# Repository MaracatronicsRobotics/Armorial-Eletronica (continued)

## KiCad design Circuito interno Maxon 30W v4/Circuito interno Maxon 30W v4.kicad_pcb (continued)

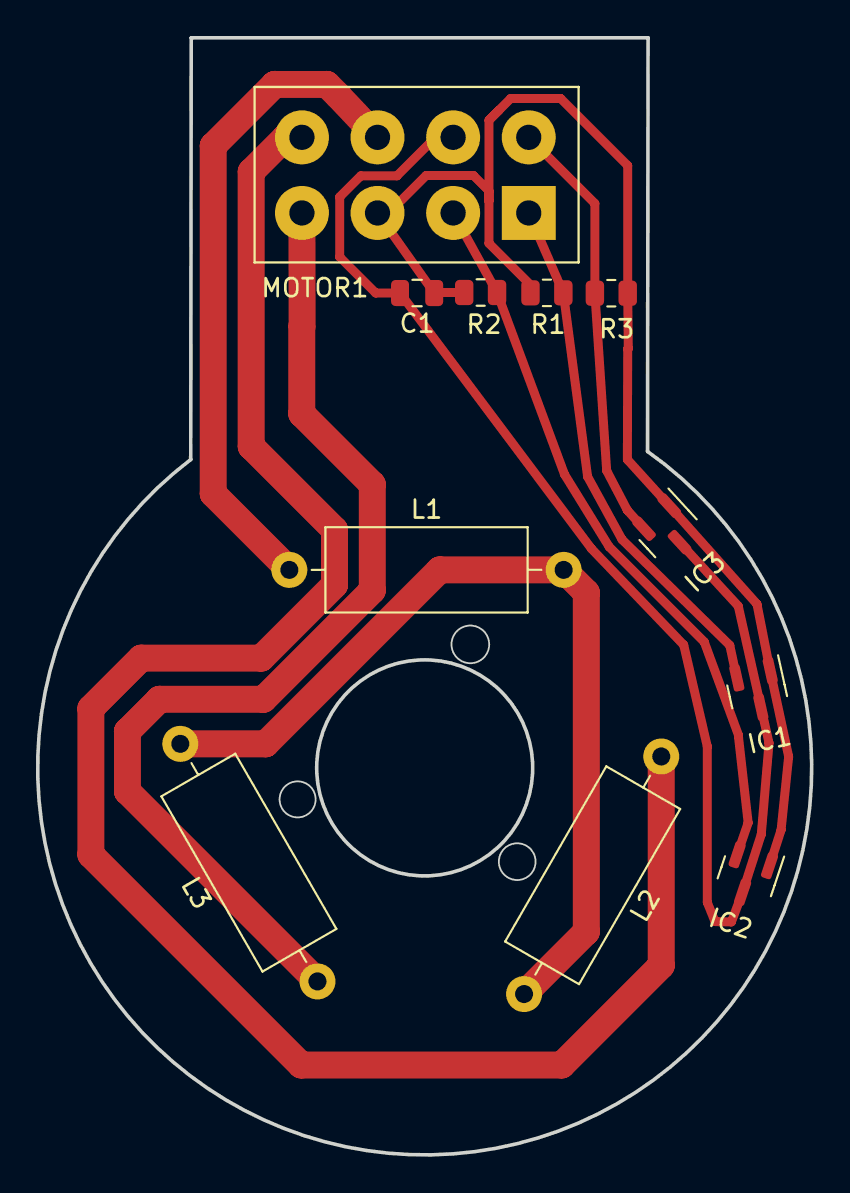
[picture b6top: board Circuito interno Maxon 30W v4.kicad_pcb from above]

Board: 2 copper layers, 43.0 x 62.1 mm, 11 parts (0 on the bottom side), 9 nets.

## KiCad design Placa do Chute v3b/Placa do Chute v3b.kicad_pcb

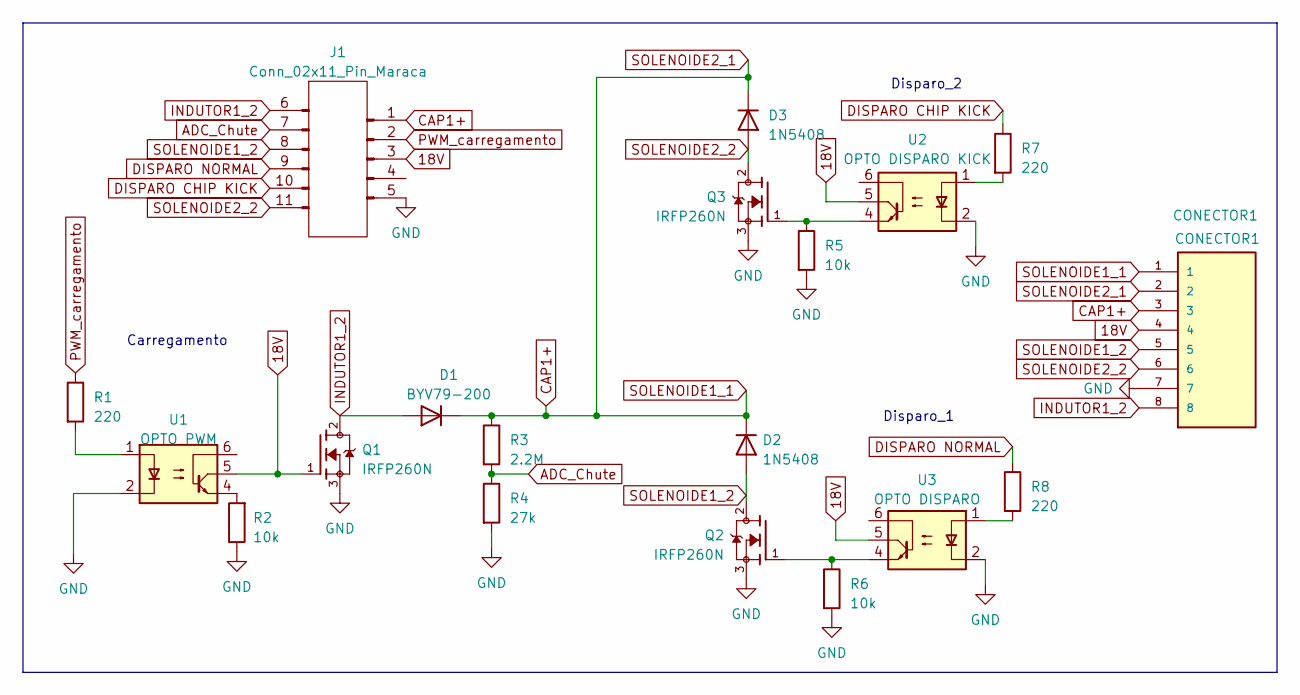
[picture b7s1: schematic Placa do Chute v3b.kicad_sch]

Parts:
CONECTOR1: CONECTOR1; TE_1586037-8b
D1: BYV79-200; TO-220-2_Vertical
D2, D3: 1N5408; D_DO-201AD_P15.24mm_Horizontal
J1: Conn_02x11_Pin_Maraca; Conn_2x11_Maraca_Chute
Q1, Q2, Q3: IRFP260N; TO545P1560X500X2460-3 90d; PARTREV 08/18/10
R1, R7, R8: 220; R_Axial_DIN0207_L6.3mm_D2.5mm_P10.16mm_Horizontal
R2, R5, R6: 10k; R_Axial_DIN0207_L6.3mm_D2.5mm_P10.16mm_Horizontal
R3: 2.2M; R_Axial_DIN0207_L6.3mm_D2.5mm_P10.16mm_Horizontal
R4: 27k; R_Axial_DIN0207_L6.3mm_D2.5mm_P10.16mm_Horizontal
U1: OPTO PWM; DIP-6_W7.62mm
U2: OPTO DISPARO KICK; DIP-6_W7.62mm
U3: OPTO DISPARO; DIP-6_W7.62mm

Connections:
18V: CONECTOR1.4, J1.3, Q1.1, U1.5, U2.5, U3.5
ADC_Chute: J1.7, R3.2, R4.1
CAP1+: CONECTOR1.1, CONECTOR1.2, CONECTOR1.3, D1.1 (K), D2.1 (K), D3.1 (K), J1.1, R3.1
DISPARO CHIP KICK: J1.10, R7.1
DISPARO NORMAL: J1.9, R8.1
GND: CONECTOR1.7, J1.5, Q1.3, Q2.3, Q3.3, R2.1, R4.2, R5.2, R6.2, U1.2, U2.2, U3.2
INDUTOR1_2: CONECTOR1.8, D1.2 (A), J1.6, Q1.2
unnamed: Q2.1, R6.1, U3.4
unnamed: Q3.1, R5.1, U2.4
unnamed: R1.2, U1.1
unnamed: R2.2, U1.4
unnamed: R7.2, U2.1
unnamed: R8.2, U3.1
PWM_carregamento: J1.2, R1.1
SOLENOIDE1_2: CONECTOR1.5, D2.2 (A), J1.8, Q2.2
SOLENOIDE2_2: CONECTOR1.6, D3.2 (A), J1.11, Q3.2

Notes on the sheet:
Disparo_2
Carregamento
Disparo_1

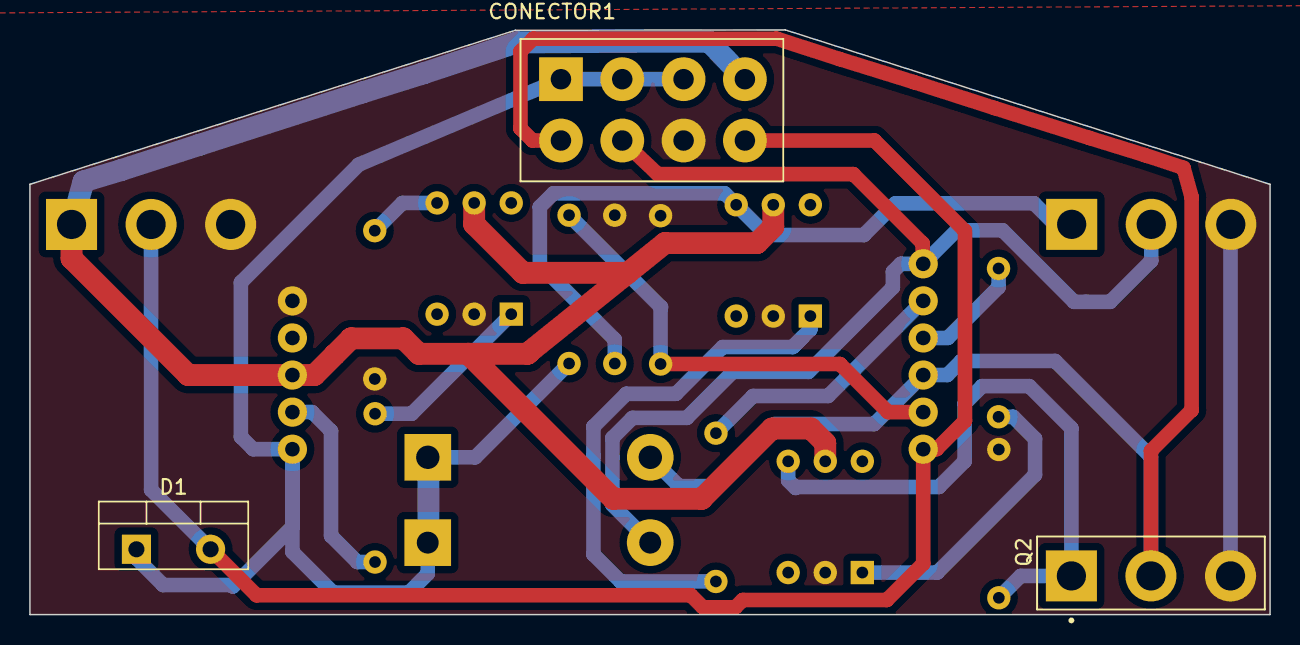
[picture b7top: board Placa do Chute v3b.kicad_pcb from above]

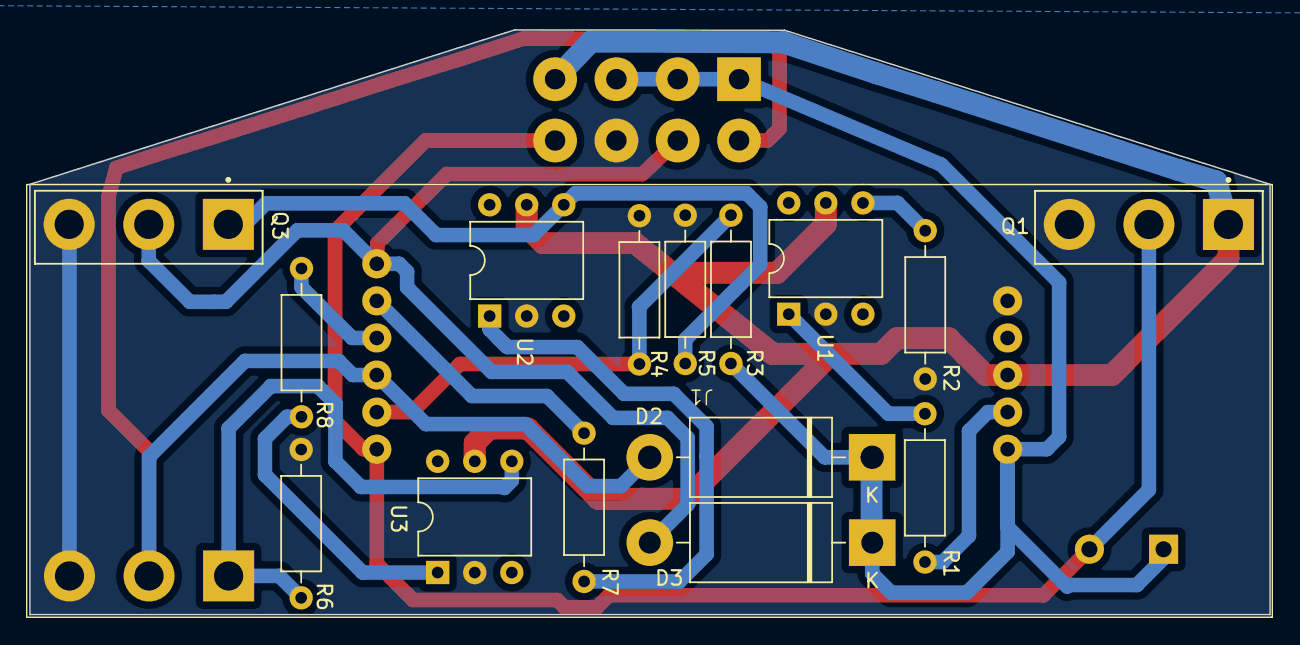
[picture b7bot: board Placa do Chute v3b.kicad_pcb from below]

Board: 2 copper layers, 84.9 x 40.0 mm, 19 parts (16 on the bottom side), 16 nets.

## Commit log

2023-10-25 placa base PTH v3
    Primeira placa que funcionou chute, locomoção e drible. Feita no Parqtel.
2023-10-25 placa SMD V9
    Placa que foi para a china e competiu na LARC 2023
2023-10-25 placa buck
    Placa feita para compor Placa SMD V9.
2023-10-26 placa do chute v1
    Feita para acoplar na placa base PTH V3
2023-10-26 placa do chute v2
    Já feita para a Placa SMD V9, porém não era possível descarregar o capacitor.
2023-10-26 placa do chute v3
    Agora com o "botão de pânico" para conseguir carregar o capacitor e desligar o robô com segurança.
2023-10-26 placa V3S v1
    Placa do v3s que jogou a RCX 2023
2023-10-26 placa V3S v2
    Placa definitiva que foi para a JLCPCB e jogou a LARC 2023
2023-10-27 placa do chute v4
    Modificações: Todos os resistores são SMD em relação a versão anterior e o botão de pânico foi trocado por um de 90 graus para obter acesso por fora do robô. FALTA REVISAR para ir pra JLCPBC
2023-10-28 Placa do Motor Maxon
2023-11-07 Ajustes na pasta
    Placa que jogou a RCX - VERSÃO 1
    Placa que jogou a LARC( e foi pra china)- VERSÃO 2
2023-11-08 Shield SX1280 v1
    Primeira versão de shield para testes do modulo de comunicação Lora SX1280.
2023-11-13 Inclusão de arquivos novos
